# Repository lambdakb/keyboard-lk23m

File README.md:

# LK23 Numpad / Macropad

## Layout

[Keyboard Layout Editor](https://www.keyboard-layout-editor.com/##@_css=.keyborder%5Bstyle*%2F=%22%23ff0000%22%5D%20%7B%0A%20%20%20%20border-radius%2F:%2050%25%20!important%2F%3B%0A%20%20%20%20background-color%2F:%20%23ccc%20!important%2F%3B%0A%7D%0A.keytop%5Bstyle*%2F=%22%23ff4223%22%5D%20%7B%0A%20%20%20%20border-radius%2F:%2050%25%20!important%2F%3B%0A%20%20%20%20background-color%2F:%20%23fff%20!important%2F%3B%0A%7D%3B&@_p=R1&a:7%3B&=%3Ci%20class%2F='kb%20kb-Multimedia-Rewind-Start'%3E%3C%2F%2Fi%3E%0A%0A%0A%0A1U&=%3Ci%20class%2F='kb%20kb-Multimedia-Play-Pause'%3E%3C%2F%2Fi%3E%0A%0A%0A%0A1U&=%3Ci%20class%2F='kb%20kb-Multimedia-FastForward-End'%3E%3C%2F%2Fi%3E%0A%0A%0A%0A1U&_c=%23ff0000&p=CHICKLET%3B&=%3Ci%20class%2F='kb%20kb-Multimedia-Volume-Up-2'%3E%3C%2F%2Fi%3E%3B&@_y:0.25&c=%23cccccc&p=R1%3B&=%3Ci%20class%2F='kb%20kb-Unicode-Lock-Closed-2'%3E%3C%2F%2Fi%3E%0A%0A%0A%0A1U&=%2F%2F%0A%0A%0A%0A1U&=*%0A%0A%0A%0A1U&=-%0A%0A%0A%0A1U%3B&@_p=R2%3B&=7%0A%0A%0A%0A1U&=8%0A%0A%0A%0A1U&=9%0A%0A%0A%0A1U&=+%0A%0A%0A%0A1U%3B&@_p=R3%3B&=4%0A%0A%0A%0A1U&=5%0A%0A%0A%0A1U&=6%0A%0A%0A%0A1U&=%3Ci%20class%2F='kb%20kb-Unicode-BackSpace-DeleteLeft-Big'%3E%3C%2F%2Fi%3E%0A%0A%0A%0A1U%3B&@_p=R4%3B&=1%0A%0A%0A%0A1U&=2%0A%0A%0A%0A1U&=3%0A%0A%0A%0A1U%3B&@_ry:5.25%3B&=0%0A%0A%0A%0A1U&=00%0A%0A%0A%0A1U&=.%0A%0A%0A%0A1U%3B&@_r:90&rx:3&y:-1&x:-1&w:2%3B&=%3Ci%20class%2F='kb%20kb-Return-2'%3E%3C%2F%2Fi%3E%0A%0A%0A%0A2U)

### Variations

This keyboard has been designed as a standalone numpad with an extra top row to be used as a macro pad or media pad, as such, it can be configured in different ways when building it.

Here is the list of supported variations:

- Optional encoder on the top left key
- Optional encoder on the top right key
- The top two center keys can be replaced by a 0.91" OLED screen

This allows for a number of configuration on the extra top row that can be used for a number of things. Each of these variations are supported in the Vial firmware under the `Layout` tab. See [Vial Layout Options](#vial-layout-options) for more details.

|    Example `#1`     |     Example `#2`      |       Example `#3`       |         Example `#4`         |
| :-----------------: | :-------------------: | :----------------------: | :--------------------------: |
| ![Example Macropad] | ![Example Media Keys] | ![Example OLED + Volume] | ![Example OLED + 2 Encoders] |

[Example Macropad]: assets/vial-macropad.png
[Example Media Keys]: assets/vial-mediapad.png
[Example OLED + Volume]: assets/vial-oled-volume.png
[Example OLED + 2 Encoders]: assets/vial-oled-knobs.png

This PCB can also be built as a wireless keyboard using a nice!nano microcontroller. See [Wireless Support](#wireless-support) for more details on how to achieve this.

<!-- TODO: Create a diagram of things that can be installed or not like the lotus 58 https://raw.githubusercontent.com/4EBOOT/Lotus58/Glow/Glow/Image/layout_variations.png  -->

## PCB

|          PCB (Front)          |         PCB (Back)          |
| :---------------------------: | :-------------------------: |
| [![PCB Front]][PCB Front PNG] | [![PCB Back]][PCB Back PNG] |

[PCB Front]: output/pcb/img/lk23m-pcb-top.svg
[PCB Front PNG]: output/pcb/img/lk23m-pcb-top.png
[PCB Back]: output/pcb/img/lk23m-pcb-bottom.svg
[PCB Back PNG]: output/pcb/img/lk23m-pcb-bottom.png

The PCB has been designed in [KiCad EDA 9.0](https://www.kicad.org/) using the [`kicad-lkbd`](https://github.com/lambdakb/kicad-lkbd) libraries and [`kbplacer`](https://github.com/adamws/kicad-kbplacer).

You can preview the project files using [KiCanvas](https://kicanvas.org/?github=https%3A%2F%2Fgithub.com%2Flambdakb%2Fkeyboard-lk23m%2Fblob%2Fmain%2Fpcb%2Flk23m-pcb.kicad_pro) directly in your browser and download the latest fabrication files for JLCPCB from the [latest release](https://github.com/lambdakb/keyboard-lk23m/releases/latest/).

The exported schematic is also available under [`output/schematics`](output/schematics/).

### PCB Order

| Parameters                       | Value                  |
| -------------------------------- | ---------------------- |
| Base Material                    | FR4                    |
| Layers                           | 2                      |
| Dimensions                       | 76.2 × 119.06 mm       |
| PCB Thickness                    | 1.6 mm                 |
| PCB Color [^pcb-color]           | Black                  |
| Silkscreen                       | White                  |
| Surface Finish [^surface-finish] | Lead Free HASL or ENIG |
| Copper Weight                    | 1 oz                   |
| Via Covering                     | Tented                 |
| Min Via Hole Size                | 0.3 mm                 |
| Board Outline Tolerance          | ± 0.2 mm               |

[^pcb-color]: You can select any PCB color you want but some manufacturers such as JLCPCB may charge you more for uncommon combos (such as Blue PCB + ENIG Surface Finish).
[^surface-finish]: The "HASL (with lead)" option is extremely discouraged due to the risk of lead poisoning. We strongly recommend paying the premium for the "Lead Free HASL" option.

### JLCPCB Specific Options

<!-- NOTE: This is generic and used for ALL LambdaKB PCBs EXCEPT for cases PCB   -->

#### Mark on PCB

The following JCLPCB specific options are used to serialize PCBs on order. An 8 × 8 mm silkscreen square was added to the PCB to allow for a 2D barcode to be added.

| Parameters            | Value                       |
| --------------------- | --------------------------- |
| Mark on PCB           | 2D barcode (Serial Number)  |
| - Printing            | 2D barcode & Number         |
| - Code Type           | Data Matrix Code            |
| - Prefix              | `LKBD_LK23M_v100`           |
| - Unique Number       | Remove                      |
| - Incrementing Number | _`YYMM01`_ (e.g.: `250300`) |
| - 2D Barcode Size     | 8 × 8 mm                    |
| - 2D Barcode Position | Specify Position            |

Serial numbers are based on the current date using the `YYMM01` format for its incrementing numbers. Orders in February 2025 would start then start it at `250300`, making the final serial `LKBD_LK23M_v100_250300`.

## Cases

### FR4

|          Plate (Top)          |           Plate (Bottom)            |      Bottom Case (Top)      |         Bottom Case (Top)         |
| :---------------------------: | :---------------------------------: | :-------------------------: | :-------------------------------: |
| [![Plate Top]][Plate Top PNG] | [![Plate Bottom]][Plate Bottom PNG] | [![Case Top]][Case Top PNG] | [![Case Bottom]][Case Bottom PNG] |

[Plate Top]: output/case/fr4/img/lk23m-plate-top.svg
[Plate Top PNG]: output/case/fr4/img/lk23m-plate-top.png
[Plate Bottom]: output/case/fr4/img/lk23m-plate-bottom.svg
[Plate Bottom PNG]: output/case/fr4/img/lk23m-plate-bottom.png
[Case Top]: output/case/fr4/img/lk23m-bottom-top.svg
[Case Top PNG]: output/case/fr4/img/lk23m-bottom-top.png
[Case Bottom]: output/case/fr4/img/lk23m-bottom-bottom.svg
[Case Bottom PNG]: output/case/fr4/img/lk23m-bottom-bottom.png

The FR4 case has also been designed in [KiCad EDA 9.0](https://www.kicad.org/) and consist of two PCBs, one for the switch plate and one for the bottom plate.

Use the same parameters present in [PCB Order](./README.md#pcb-order) to order the plate and bottom PCB. For JLCPCB orders, you can select "Remove Mark" for the "Mark on PCB" option as there is no need to serialize the case itself. You can find the fabrication files in [`output/case/fr4/fabrication/jlcpcb`](output/case/fr4/fabrication/jlcpcb/).

If you prefer to fabricate them by any other mean (such as laser cut acrylic), you can download their board outlines as `DXF` in [`output/case/dxf`](output/case/dxf).

## BOM

| Part                   | Ref.                                                                                 | Quantity | Optional | Remarks                                                                                                                                                              |
| ---------------------- | ------------------------------------------------------------------------------------ | :------: | :------: | -------------------------------------------------------------------------------------------------------------------------------------------------------------------- |
| PCB                    | [LK23M PCB](./README.md#pcb)                                                         |    1     |    ❌    | See [PCB](./README.md#pcb) section on how to order it.                                                                                                               |
| Top Plate              | [FR4 Top Plate](./README.md#fr4)                                                     |    1     |    ✅    | Optional if using an alternative case.                                                                                                                               |
| Bottom Plate           | [FR4 Bottom Plate](./README.md#fr4)                                                  |    1     |    ✅    | Optional if using an alternative case.                                                                                                                               |
| Case Screws            | [M2 × 4 mm Low Profile Socket Head Screw (Hex)]                                      |    8     |    ✅    | Optional if using an alternative case. Low profile hex head screws are recommended, but any head type should be compatible. Screws up to 8 mm in length should work. |
| Case Standoffs         | [M2 × 12 mm Brass Hex Standoff]                                                      |    4     |    ✅    | Optional if using an alternative case. Longer / shorter standoff could work depending on how the controller is mounted and if using a battery.                       |
| Pro Micro Controller   | [Arduino Pro Micro 5V], [Adafruit KB2040] or [nice!nano]                             |    1     |    ❌    | Supports various Pro Micro style controller (including RP2040 based ones) as well as the nice!nano for wireless builds. [^wireless]                                  |
| MCU Socket             | [DIP-24 Round Socket (Wide, 15.24 mm)]                                               |    1     |    ✅    | Recommended to socket the controller, can be omitted if soldered directly. Compatibles pins are required such as dismantled [LED strip male adapters].               |
| Reset Push Button      | [DIP 2pin Momentary Push Button (6 × 3.5 mm)] (THT)                                  |    1     |    ✅    | Used as a reset switch, can be omitted if you flash the controller before installing it or if the controller can be put in bootloader mode from any other means.     |
| 1N418 Diodes           | [1N4148W T4 SOD-323] (SMD) or [1N4148 DO-35] (THT)                                   |  21-23   |    ❌    | Only 21 diodes are needed if the OLED screen is installed.                                                                                                           |
| Kailh Hot-Swap Sockets | [CPG151101S11-16] (SMD)                                                              |    19    |    ✅    | The top 4 keys can not be made hot-swappable due to size constraint and need to be soldered directly. All switches can be soldered directly to the PCB if preferred. |
| Key Switches           | Any [Cherry MX] Compatible Switch                                                    |  19-23   |    ❌    | Amount depends on the variant built, a two encoder OLED setup would require 2 EC12 encoder and 19 MX switches, while the key switches only variant needs 23.         |
| 2U Stabilizer          | Any standard [2U PCB mounted MX stabilizer]                                          |    1     |    ✅    | Recommended for Enter key stability.                                                                                                                                 |
| Rotary Encoder(s)      | Any [EC11] / [EC12] style 5-pin Encoder                                              |   0-2    |    ✅    | Optional, can be installed in place of the top left and/or top right most switches.                                                                                  |
| 100nF Capacitor(s)     | [1206 SMD Ceramic Capacitor] (SMD) or [104 Ceramic Disk Capacitor (5 × 2.5mm)] (THT) |   0-4    |    ✅    | Two recommended per encoder for noise filtering.                                                                                                                     |
| 0.91" OLED Display     | [SSD1306 0.91" 128X32 OLED I²C Display Module]                                       |   0-1    |    ✅    | Optional, replace the top middle two switches.                                                                                                                       |
| Power Slide Switch     | [PCM12SMTR] (SMD) or [MSK-12C02] (SMD)                                               |    1     |    ✅    | Only required for battery powered wireless builds. [^wireless]                                                                                                       |
| Battery Connector      | [JST-PH 2pin right-angle Male Connector]                                             |    1     |    ✅    | Only needed for battery powered wireless builds if the battery is not soldered directly to the board (recommended). [^wireless]                                      |
| 3.7V Li-Po Battery     | [603449 (1100 mAh)] or [503450 (1000 mAh)] 3.7V Li-Po Battery                        |    1     |    ✅    | Only required for battery powered wireless builds, any 3.7 V (1 Cell) Li-Po battery slimmer than 8 mm with a JST-PH connector should work. [^wireless]               |

<!-- NOTE: should we create a separate BOM for the case if we provide two different case ? -->

[M2 × 4 mm Low Profile Socket Head Screw (Hex)]: https://www.aliexpress.com/item/4001072025844.html
[M2 × 12 mm Brass Hex Standoff]: https://www.aliexpress.com/item/1005006049595637.html
[Arduino Pro Micro 5V]: https://www.sparkfun.com/pro-micro-5v-16mhz.html
[Adafruit KB2040]: https://www.adafruit.com/product/5302
[nice!nano]: https://nicekeyboards.com/nice-nano/
[DIP-24 Round Socket (Wide, 15.24 mm)]: https://www.aliexpress.com/item/1005005770166098.html
[LED strip male adapters]: (https://www.aliexpress.com/item/1005005742644313.html)
[1N4148W T4 SOD-323]: https://www.aliexpress.com/item/1005006127619725.html
[1N4148 DO-35]: https://www.aliexpress.com/item/4000142272546.html
[CPG151101S11-16]: https://www.aliexpress.com/item/1005007052649640.html
[Cherry MX]: https://www.aliexpress.com/item/1005006255961111.html
[2U PCB mounted MX stabilizer]: https://www.aliexpress.com/item/1005004229140548.html
[EC11]: https://www.aliexpress.com/item/32382989585.html
[EC12]: https://www.aliexpress.com/item/1005005196870256.html
[1206 SMD ceramic capacitor]: https://www.aliexpress.com/item/32966490820.html
[104 Ceramic Disk Capacitor (5 × 2.5mm)]: https://www.aliexpress.com/item/32971478818.html
[DIP 2pin Momentary Push Button (6 × 3.5 mm)]: https://www.aliexpress.com/item/1005001849576755.html
[SSD1306 0.91" 128X32 OLED I²C Display Module]: https://www.aliexpress.com/item/32777216785.html
[PCM12SMTR]: https://www.digikey.com/en/products/detail/c-k/PCM12SMTR/1640112
[MSK-12C02]: https://www.aliexpress.com/item/4000685483225.html
[JST-PH 2pin right-angle Male Connector]: https://www.aliexpress.com/item/1005004955655144.html
[603449 (1100 mAh)]: https://amzn.eu/d/e3uVbqB
[503450 (1000 mAh)]: https://aliexpress.com/item/1005003198563309.html

[^wireless]: See [Wireless Support](./README.md#wireless-support) for more details.

## Firmware

The pre-build firmware available in this repository are compiled using [Vial](https://get.vial.today/) (a fork of [QMK](https://qmk.fm) allowing customization via a GUI).

As per the original license of both Vial and QMK, the firmware itself is licensed under the GPLv3 license and its source code is available at [`vial-qmk/keyboards/lambdakb/lk23m`](https://github.com/lambdakb/vial-qmk/tree/lambdakb/keyboards/lambdakb/lk23m).

### Default Vial Keymap

| Layer 0           | Layer 1                        |
| ----------------- | ------------------------------ |
| ![Keymap Layer 0] | ![Keymap Layer 1] |

[Keymap Layer 0]: assets/vial-default-layer0.png
[Keymap Layer 1]: assets/vial-default-layer1.png

### Vial Layout Options

| Default           | Disable Left Encoder           | Disable Right Encoder           | OLED Screen in Center           |
| ----------------- | ------------------------------ | ------------------------------- | ------------------------------- |
| ![Layout Default] | ![Layout Disable Left Encoder] | ![Layout Disable Right Encoder] | ![Layout OLED Screen in Center] |

[Layout Default]: assets/vial-layout-default.png
[Layout Disable Left Encoder]: assets/vial-layout-left-encoder.png
[Layout Disable Right Encoder]: assets/vial-layout-right-encoder.png
[Layout OLED Screen in Center]: assets/vial-layout-oled-screen.png

Each of these options can be combined to match the physical layout of your build.

## Wireless Support

To add wireless support to this keyboard, you will need a controller that provides power input and a charging circuit between the top RAW and GND such as the `nice!nano`.

The PCB itself provides a way to attach a JST-PH connector as well as a slide switch for power management. This slide switch must be set to ON for the charging circuit to work.

This hasn't been extensively tested yet and should be considered experimental (no wireless firmware will be provided for now). The feature was added to the PCB as way for us to prototype a potential wireless keyboard.

## License

This design is licensed under the [Creative Commons Attribution-NonCommercial-ShareAlike 4.0 International License (CC BY-NC-SA 4.0)](https://creativecommons.org/licenses/by-nc-sa/4.0/).

You are free to use, share, and adapt the design for non-commercial purposes, provided that:

- **Attribution**: Proper credit must be given, a link to the license provided, and any changes indicated.
- **NonCommercial**: The material cannot be used for commercial purposes without prior approval.
- **ShareAlike**: Any derivative works must be distributed under the same license.

If you are a retailer or business interested in selling this design or products derived from it, I am open to granting commercial licenses on a case-by-case basis. Please feel free to contact me to discuss terms.

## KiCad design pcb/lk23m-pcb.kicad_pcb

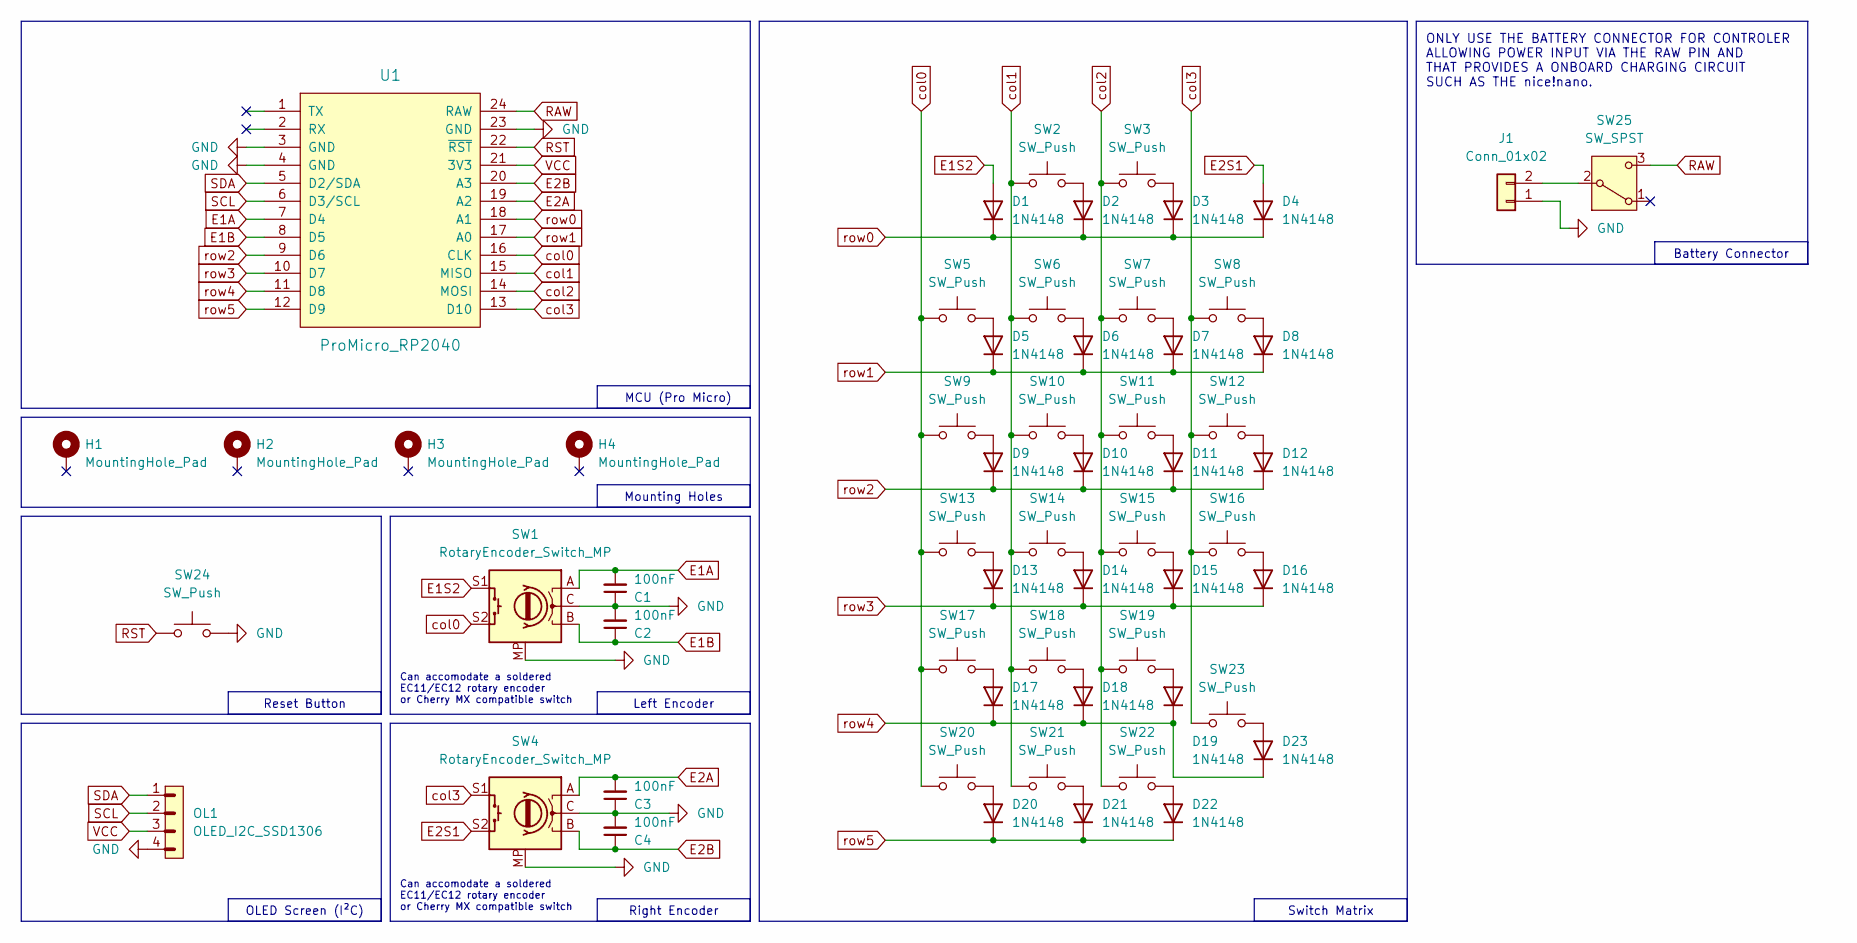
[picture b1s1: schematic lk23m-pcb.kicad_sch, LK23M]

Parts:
C1, C2, C3, C4: 100nF; Capacitor_SMD+THT_1206_5.0x2.5mm_P5.00mm; LCSC C24497
D1, D2, D3, D4, D5, D6, D7, D8, D9, D10, D11, D12, D13, D14, D15, D16, D17, D18, D19, D20, D21, D22, D23: 1N4148; Diode_SMD+THT_SOD123_DO35_P6.5mm; LCSC C81598
H1, H2, H3, H4: MountingHole_Pad; MountingHole_2.2mm_M2_ISO14580_Pad
J1: Conn_01x02; JST_PH_S2B-PH-K_1x02_P2.00mm_Horizontal
OL1: OLED_I2C_SSD1306; OLED_SSD1306_128x32_0.91inch_I2C_btmSilk
SW1, SW4: RotaryEncoder_Switch_MP; SW_MX_EC11_THT_sqSilk
SW2, SW3: SW_Push; SW_MX_THT_sqSilk
SW5, SW6, SW7, SW8, SW9, SW10, SW11, SW12, SW13, SW14, SW15, SW16, SW17, SW18, SW19, SW20, SW21, SW22, SW23: SW_Push; SW_MX_HotSwap_THT_sqSilk; LCSC C41430893
SW24: SW_Push; SW_Push_1P1T_6x3.5mm
SW25: SW_SPST; SW_SPDT_PCM12; LCSC C221841
U1: ProMicro_RP2040; MCU_KB2040_DIP-24_Socket_Reverse

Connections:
E1A: C1.2, SW1.A, U1.7 (D4)
E1B: C2.1, SW1.B, U1.8 (D5)
E1S2: D1.2 (A), SW1.S1
E2A: C3.2, SW4.A, U1.19 (A2)
E2B: C4.1, SW4.B, U1.20 (A3)
E2S1: D4.2 (A), SW4.S2
GND: C1.1, C2.2, C3.1, C4.2, J1.1, OL1.4, SW1.C, SW1.MP, SW4.C, SW4.MP, SW24.2, U1.3 (GND), U1.4 (GND), U1.23 (GND)
unnamed: D2.2 (A), SW2.2
unnamed: D3.2 (A), SW3.2
unnamed: D5.2 (A), SW5.2
unnamed: D6.2 (A), SW6.2
unnamed: D7.2 (A), SW7.2
unnamed: D8.2 (A), SW8.2
unnamed: D9.2 (A), SW9.2
unnamed: D10.2 (A), SW10.2
unnamed: D11.2 (A), SW11.2
unnamed: D12.2 (A), SW12.2
unnamed: D13.2 (A), SW13.2
unnamed: D14.2 (A), SW14.2
unnamed: D15.2 (A), SW15.2
unnamed: D16.2 (A), SW16.2
unnamed: D17.2 (A), SW17.2
unnamed: D18.2 (A), SW18.2
unnamed: D19.2 (A), SW19.2
unnamed: D20.2 (A), SW20.2
unnamed: D21.2 (A), SW21.2
unnamed: D22.2 (A), SW22.2
unnamed: D23.2 (A), SW23.2
unnamed: J1.2, SW25.2 (B)
RAW: SW25.3 (C), U1.24 (RAW)
RST: SW24.1, U1.22 (~RST)
SCL: OL1.2, U1.6 (D3/SCL)
SDA: OL1.1, U1.5 (D2/SDA)
VCC: OL1.3, U1.21 (3V3)
col0: SW1.S2, SW5.1, SW9.1, SW13.1, SW17.1, SW20.1, U1.16 (CLK)
col1: SW2.1, SW6.1, SW10.1, SW14.1, SW18.1, SW21.1, U1.15 (MISO)
col2: SW3.1, SW7.1, SW11.1, SW15.1, SW19.1, SW22.1, U1.14 (MOSI)
col3: SW4.S1, SW8.1, SW12.1, SW16.1, SW23.1, U1.13 (D10)
row0: D1.1 (K), D2.1 (K), D3.1 (K), D4.1 (K), U1.18 (A1)
row1: D5.1 (K), D6.1 (K), D7.1 (K), D8.1 (K), U1.17 (A0)
row2: D9.1 (K), D10.1 (K), D11.1 (K), D12.1 (K), U1.9 (D6)
row3: D13.1 (K), D14.1 (K), D15.1 (K), D16.1 (K), U1.10 (D7)
row4: D17.1 (K), D18.1 (K), D19.1 (K), D23.1 (K), U1.11 (D8)
row5: D20.1 (K), D21.1 (K), D22.1 (K), U1.12 (D9)

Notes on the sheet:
Mounting Holes
OLED Screen (I²C)
Reset Button
MCU (Pro Micro)
Right Encoder
Left Encoder
Can accomodate a soldered EC11/EC12 rotary encoder or Cherry MX compatible switch
Switch Matrix
ONLY USE THE BATTERY CONNECTOR FOR CONTROLER ALLOWING POWER INPUT VIA THE RAW PIN AND THAT PROVIDES A ONBOARD CHARGING CIRCUIT SUCH AS THE nice!nano.
Battery Connector

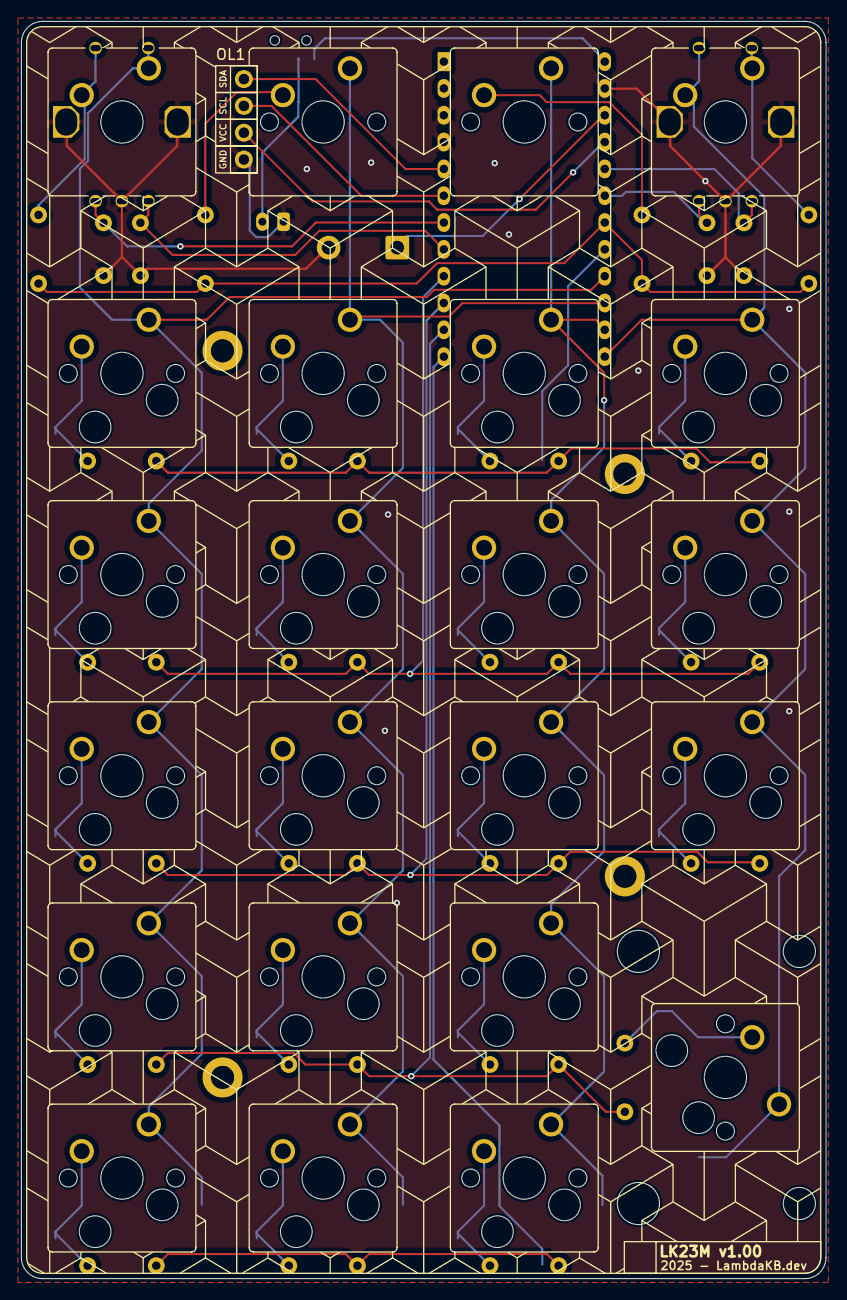
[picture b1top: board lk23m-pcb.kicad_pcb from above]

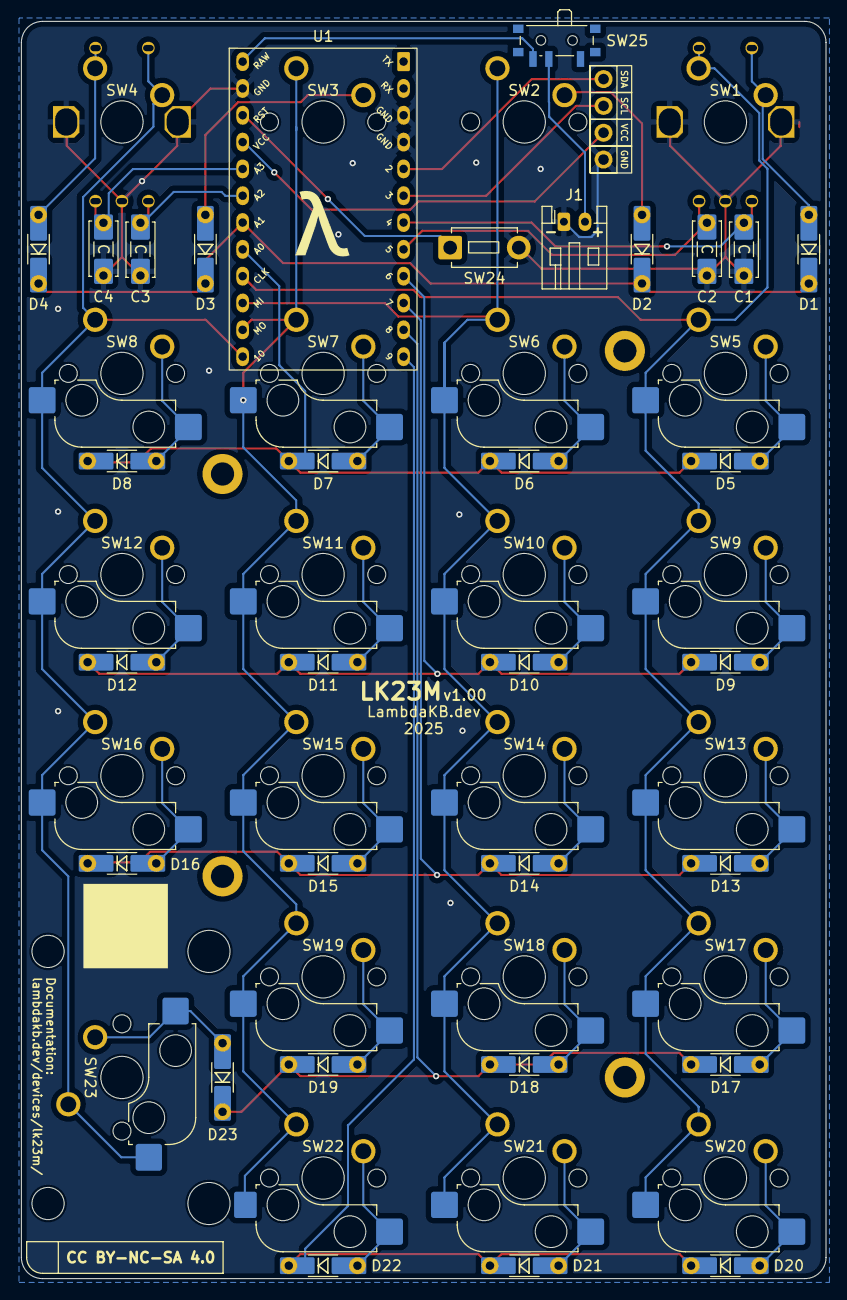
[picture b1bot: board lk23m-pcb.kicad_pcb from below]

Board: 2 copper layers, 76.2 x 119.1 mm, 60 parts (50 on the bottom side), 44 nets.

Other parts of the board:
STAB23: Stabilizer_MX_2U

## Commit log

2024-12-28 Init KiCad project
2025-01-20 Add firt draft of the keyboard PCB, assets and tools
2025-01-20 Add FR4 PCB Case
2025-01-20 Migrate to using symbols and footprints from gtihub.com/lambdakb/kicad-lkbd
2025-01-20 Model should be done, we should just look at exporting keyboard.pretty as a library
2025-01-20 Move KiBot config to reusable folder and fix PCBDraw output
2025-01-20 Fix SMD footprint position + add kibot setup
2025-01-20 Rename PCB project to prepare for release
2025-01-20 Move kibot wrapper script to `.kibot/bin`
2025-01-20 Add LICENSE file
2025-01-21 Add output folder and update README.md
2025-01-23 Update LKBD libraries
2025-01-23 Update LICENSE document to Markdown
2025-02-03 Use a JST-PH Right Angle connector for battery
2025-02-03 Link to PNG preview in README.md
2025-02-04 Cleanup schematic and pcb
2025-02-06 Add BOM and layouts to README.md
2025-02-06 Cleanup examples
2025-02-06 Add notes about Wireless support
2025-02-06 move things around
2025-02-07 Add BOM and Vial layouts to README.md (#1)
    * Add BOM and layouts to README.md
    * Cleanup examples
    * Add notes about Wireless support
    * move things around
2025-02-07 Add Silkscreen version of the FR4 Case + JLCPCB order table
2025-02-07 Add Silkscreen version of the FR4 Case + JLCPCB order table (#2)
2025-02-09 Fix README links
2025-02-09 Refactor the KiBot pipelines
2025-02-19 Use kibot:dev for now & track .zip via LFS
2025-02-19 Refactor the KiBot pipelines (#3)
2025-02-19 Regenerate missing FR4 case images
2025-02-19 Regenerate missing FR4 case images (#4)
2025-02-19 Export case DXF using centerline
2025-02-19 Remove old export
2025-02-19 Fix case DXF export (use centerline instead of polygon) (#5)
2025-02-19 Fix missed part of the pattern (was still soldermask while it should have silkscreen)
2025-02-19 Add clearance for OLED screen to plate
2025-02-19 Export
2025-02-21 Only support one case, if we want an ENIG variant we can modify it on the fly
2025-02-21 Cleanup paths in kicad_pro
2025-02-21 Fix reset switch position in FR4 case
2025-02-22 Make reusable kibot configs use definitions where they can
2025-03-18 Add clearance for OLED screen in the FR4 Plate (#6)
    * Fix missed part of the pattern (was still soldermask while it should have silkscreen)
    * Add clearance for OLED screen to plate
    * Only support one case, if we want an ENIG variant we can modify it on the fly
    * Cleanup paths in kicad_pro
    * Fix reset switch position in FR4 case
    * Make reusable kibot configs use definitions where they can
2025-03-18 Upgrade KiBot to use KiCad 9
2025-03-18 Upgrade project to KiCad 9 & cleanup FR4 plate pattern
2025-03-18 Upgrade project to KiCad 9 & cleanup FR4 plate pattern (#7)
    * Upgrade KiBot to use KiCad 9
    * Upgrade project to KiCad 9 & cleanup FR4 plate pattern
2025-03-28 Various README and Makefile fixes
2025-03-28 Various README and Makefile fixes (#8)
2025-04-12 Update LKBD and use new SW+Stab layout
2025-04-12 Update LKBD and use new SW+Stab layout (#9)
2025-04-14 Add default layout to README
2025-04-14 Add default layout to README (#10)
2025-05-13 Remove unused file

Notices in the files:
README.md:
License:
This design is licensed under the [Creative Commons Attribution-NonCommercial-ShareAlike 4.0 International License (CC BY-NC-SA 4.0)](https://creativecommons.org/licenses/by-nc-sa/4.0/).
You are free to use, share, and adapt the design for non-commercial purposes, provided that:
- **Attribution**: Proper credit must be given, a link to the license provided, and any changes indicated.
- **NonCommercial**: The material cannot be used for commercial purposes without prior approval.
- **ShareAlike**: Any derivative works must be distributed under the same license.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
